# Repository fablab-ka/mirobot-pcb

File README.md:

# mirobot-pcb
PCB for the mirobot project, using Arduino Nano and ESP-Witty

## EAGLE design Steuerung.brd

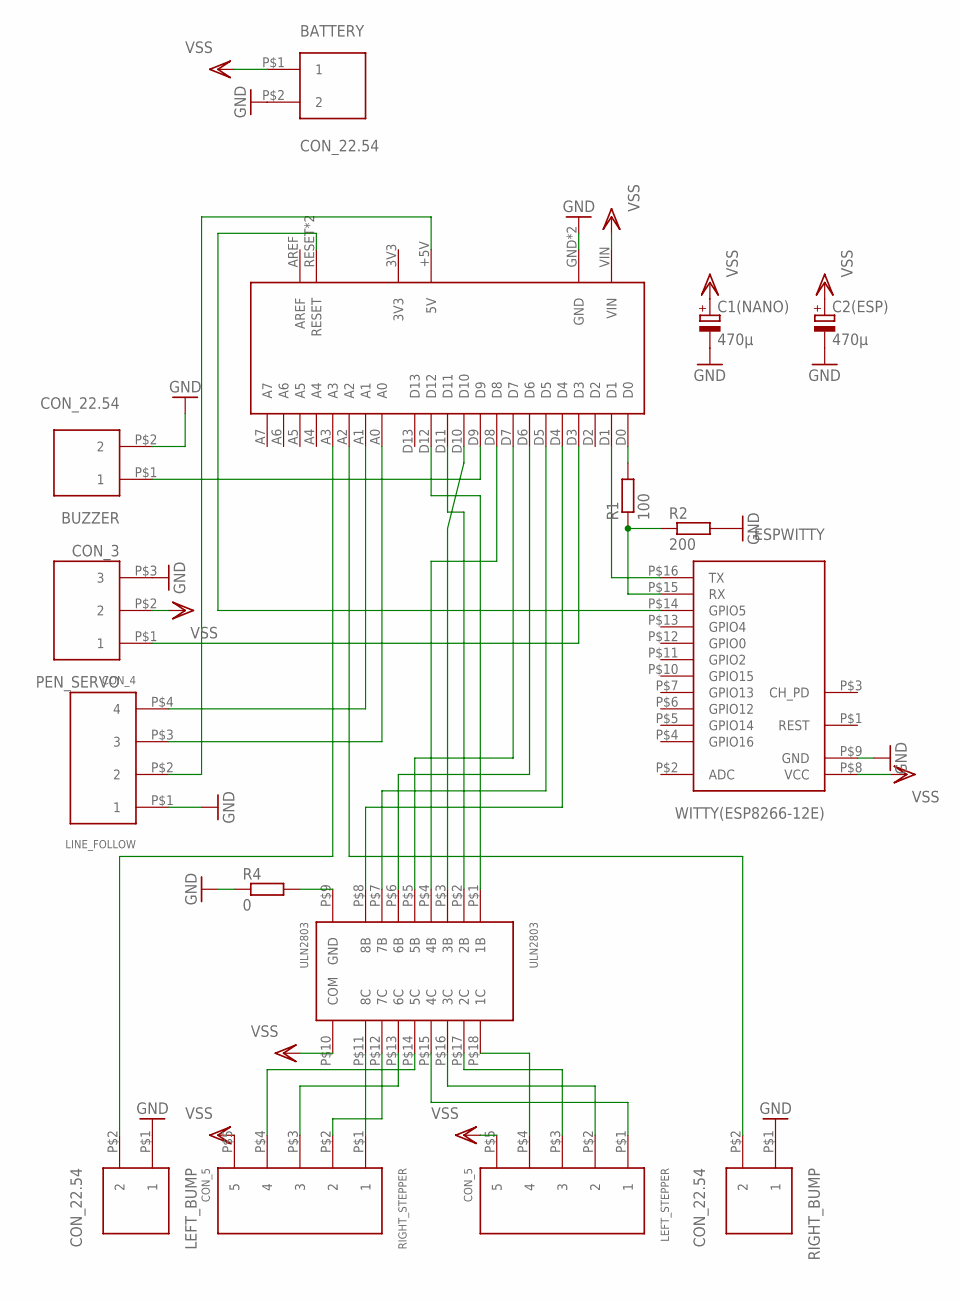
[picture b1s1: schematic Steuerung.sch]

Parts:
ARDUINO_NANO: ARDUINO_NANO
BATTERY: CON_22.54; CON_2_2.54
BUZZER: CON_22.54; CON_2_2.54
C1(NANO), C2(ESP): 470µ; E2,5-7
LEFT_BUMP: CON_22.54; CON_2_2.54
LEFT_STEPPER: CON_5; CON_5_2.54
LINE_FOLLOW: CON_4; CON_4_2.54
PEN_SERVO: CON_3; CON_3_2.54
R1: 100; 0204/7
R2: 200; 0204/7
R4: 0; R1206
RIGHT_BUMP: CON_22.54; CON_2_2.54
RIGHT_STEPPER: CON_5; CON_5_2.54
ULN2803: ULN2803; DIP_18
WITTY(ESP8266-12E): ESPWITTY; ESP-WITTY

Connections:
GND: ARDUINO_NANO.GND, ARDUINO_NANO.GND2 (GND), BATTERY.P$2 (2), BUZZER.P$2 (2), C1(NANO).-, C2(ESP).-, LEFT_BUMP.P$1 (1), LINE_FOLLOW.P$1 (1), PEN_SERVO.P$3 (3), R2.2, R4.1, RIGHT_BUMP.P$1 (1), WITTY(ESP8266-12E).P$9 (GND)
unnamed: LEFT_STEPPER.P$4 (4), ULN2803.P$18 (1C)
unnamed: LEFT_STEPPER.P$3 (3), ULN2803.P$17 (2C)
unnamed: LEFT_STEPPER.P$2 (2), ULN2803.P$16 (3C)
unnamed: LEFT_STEPPER.P$1 (1), ULN2803.P$15 (4C)
unnamed: RIGHT_STEPPER.P$4 (4), ULN2803.P$14 (5C)
unnamed: RIGHT_STEPPER.P$3 (3), ULN2803.P$13 (6C)
unnamed: RIGHT_STEPPER.P$2 (2), ULN2803.P$12 (7C)
unnamed: RIGHT_STEPPER.P$1 (1), ULN2803.P$11 (8C)
unnamed: ARDUINO_NANO.D8, ULN2803.P$4 (4B)
unnamed: ARDUINO_NANO.D10, ULN2803.P$3 (3B)
unnamed: ARDUINO_NANO.D11, ULN2803.P$2 (2B)
unnamed: ARDUINO_NANO.D12, ULN2803.P$1 (1B)
unnamed: ARDUINO_NANO.D7, ULN2803.P$5 (5B)
unnamed: ARDUINO_NANO.D6, ULN2803.P$6 (6B)
unnamed: ARDUINO_NANO.D5, ULN2803.P$7 (7B)
unnamed: ARDUINO_NANO.D4, ULN2803.P$8 (8B)
unnamed: ARDUINO_NANO.A2, RIGHT_BUMP.P$2 (2)
unnamed: ARDUINO_NANO.D0, R1.2
unnamed: R1.1, R2.1, WITTY(ESP8266-12E).P$15 (RX)
unnamed: ARDUINO_NANO.D1, WITTY(ESP8266-12E).P$16 (TX)
unnamed: ARDUINO_NANO.RESET, ARDUINO_NANO.RST (RESET), WITTY(ESP8266-12E).P$14 (GPIO5)
unnamed: ARDUINO_NANO.D9, BUZZER.P$1 (1)
unnamed: ARDUINO_NANO.D3, PEN_SERVO.P$1 (1)
unnamed: ARDUINO_NANO.A1, LINE_FOLLOW.P$4 (4)
unnamed: ARDUINO_NANO.A0, LINE_FOLLOW.P$3 (3)
unnamed: ARDUINO_NANO.A3, LEFT_BUMP.P$2 (2)
unnamed: R4.2, ULN2803.P$9 (GND)
unnamed: ARDUINO_NANO.+5V (5V), LINE_FOLLOW.P$2 (2)
VSS: ARDUINO_NANO.VIN, BATTERY.P$1 (1), C1(NANO).+, C2(ESP).+, LEFT_STEPPER.P$5 (5), PEN_SERVO.P$2 (2), RIGHT_STEPPER.P$5 (5), ULN2803.P$10 (COM), WITTY(ESP8266-12E).P$8 (VCC)

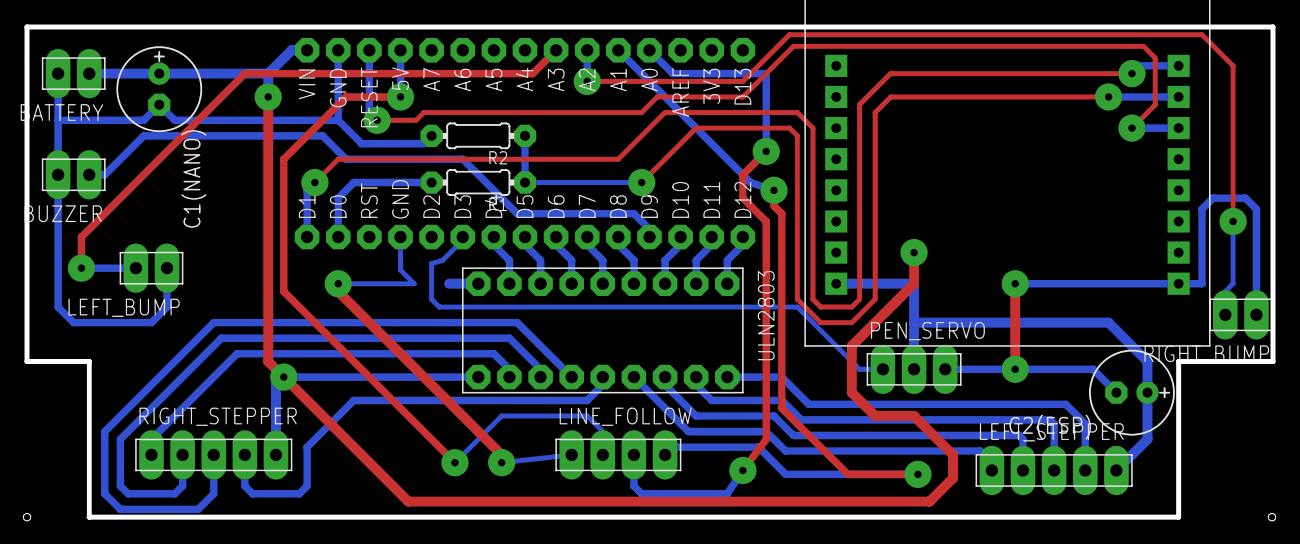
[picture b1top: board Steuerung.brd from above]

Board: 2 copper layers, 101.7 x 40.0 mm, 16 parts (1 on the bottom side), 30 nets.

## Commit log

2016-08-17 First draft
    Added library and rudimentary .sch/.brd
2016-08-19 Schaltplan für 16MHz/5V Nano und ESP-Witty adaptiert
2016-08-19 minor correction
2016-08-19 First PCB
2016-08-20 optimized Layout
    Bigger Vias and Pads, stylish 45°-edges ;)
2016-08-20 PCB resize, origin point fix
    PCB compressed (Y-axis) to fit 2 PCBs on a 160x100cm Sheet.
    Adjusted origin point in Y-Axis.
2016-10-11 PCB Resize
    Made the PCB even smaller to be millable on the Proxxon MF 70.
    This is the Version currently being tested in the Lab.
